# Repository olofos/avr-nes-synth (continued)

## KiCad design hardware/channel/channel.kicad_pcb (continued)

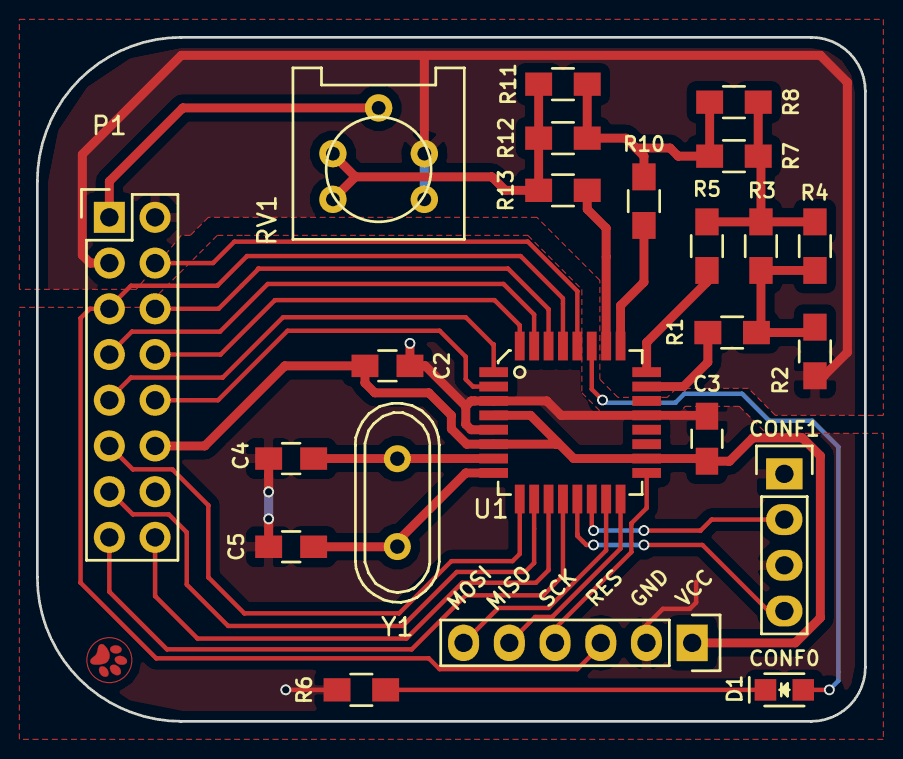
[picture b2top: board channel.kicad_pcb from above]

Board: 2 copper layers, 46.0 x 38.0 mm, 23 parts (0 on the bottom side), 32 nets.

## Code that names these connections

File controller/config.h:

#ifndef CONFIG_H_
#define CONFIG_H_

#include <avr/pgmspace.h>

#include "../common-config.h"

#define MAJOR_VERSION 0
#define MINOR_VERSION 1
#define COPYRIGHT_YEAR "2016-17"
#define AUTHOR "OOS"

#define BAUD 19200UL
#define SCL_CLOCK  100000UL

#define LOG_USE_I2C
#define LOG_USE_SSD1306
#define LOG_USE_BUF


//// Pins /////////////////////////////////////////////////////////////////////

// Bus out

#define PINS_BUS_PORT      PORTD
#define PINS_BUS_PIN       PIND
#define PINS_BUS_DDR       DDRD

#define PIN_BUS0           PORTD0
#define PIN_BUS1           PORTD1
#define PIN_BUS2           PORTD2
#define PIN_BUS3           PORTD3
#define PIN_BUS4           PORTD4
#define PIN_BUS5           PORTD5
#define PIN_BUS6           PORTD6
#define PIN_BUS7           PORTD7

#define PINS_BUS_MASK      (_BV(PIN_BUS0) | _BV(PIN_BUS1) | _BV(PIN_BUS2) | _BV(PIN_BUS3) | _BV(PIN_BUS4) | _BV(PIN_BUS5) | _BV(PIN_BUS6) | _BV(PIN_BUS7))

// Bus clock

#define PIN_DCLK           PORTB0
#define PIN_DCLK_PORT      PORTB
#define PIN_DCLK_PIN       PINB
#define PIN_DCLK_DDR       DDRB

// Frame clock

#define PIN_FCLK           PORTC3
#define PIN_FCLK_PORT      PORTC
#define PIN_FCLK_PIN       PINC
#define PIN_FCLK_DDR       DDRC

// SPI + SD card

#define PIN_SD_CD          PORTB1
#define PIN_SD_CD_PORT     PORTB
#define PIN_SD_CD_PIN      PINB
#define PIN_SD_CD_DDR      DDRB

#define PIN_SD_CS          PORTB2
#define PIN_SD_CS_PORT     PORTB
#define PIN_SD_CS_PIN      PINB
#define PIN_SD_CS_DDR      DDRB

#define PIN_MOSI          PORTB3
#define PIN_MOSI_PORT     PORTB
#define PIN_MOSI_PIN      PINB
#define PIN_MOSI_DDR      DDRB

#define PIN_MISO          PORTB4
#define PIN_MISO_PORT     PORTB
#define PIN_MISO_PIN      PINB
#define PIN_MISO_DDR      DDRB

#define PIN_SCK           PORTB5
#define PIN_SCK_PORT      PORTB
#define PIN_SCK_PIN       PINB
#define PIN_SCK_DDR       DDRB

// I2C

#define PIN_SDA           PORTC4
#define PIN_SDA_PORT      PORTC
#define PIN_SDA_PIN       PINC
#define PIN_SDA_DDR       DDRC

#define PIN_SCL           PORTC5
#define PIN_SCL_PORT      PORTC
#define PIN_SCL_PIN       PINC
#define PIN_SCL_DDR       DDRC

// IO interrupt

#define PIN_IO_INT        PORTC0
#define PIN_IO_INT_PORT   PORTC
#define PIN_IO_INT_PIN    PINC
#define PIN_IO_INT_DDR    DDRC

// LED

#define PIN_LED           PORTC1
#define PIN_LED_PORT      PORTC
#define PIN_LED_PIN       PINC
#define PIN_LED_DDR       DDRC

// Channel reset

#define PIN_CH_RESET      PORTC2
#define PIN_CH_RESET_PORT PORTC
#define PIN_CH_RESET_PIN  PINC
#define PIN_CH_RESET_DDR  DDRC



#endif

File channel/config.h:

#ifndef CONFIG_H_
#define CONFIG_H_

// GPIOR0 bits

#define CONF0_BIT          0
#define CONF1_BIT          1
#define FRAME_FLAG_BIT     2
#define SHIFT_MODE_BIT     7

#ifdef AVR

// Audio out

#define PINS_DAC_PORT      PORTC
#define PINS_DAC_DDR       DDRC

#define PIN_DAC0           PORTC0
#define PIN_DAC1           PORTC1
#define PIN_DAC2           PORTC2
#define PIN_DAC3           PORTC3

#define PINS_DAC_MASK      (_BV(PIN_DAC0) | _BV(PIN_DAC1) | _BV(PIN_DAC2) | _BV(PIN_DAC3))


// Bus in

#define PINS_BUS_PORT      PORTD
#define PINS_BUS_PIN       PIND
#define PINS_BUS_DDR       DDRB

#define PIN_BUS0           PORTD0
#define PIN_BUS1           PORTD1
#define PIN_BUS2           PORTD2
#define PIN_BUS3           PORTD3
#define PIN_BUS4           PORTD4
#define PIN_BUS5           PORTD5
#define PIN_BUS6           PORTD6
#define PIN_BUS7           PORTD7

#define PINS_BUS_MASK      (_BV(PIN_BUS0) | _BV(PIN_BUS1) | _BV(PIN_BUS2) | _BV(PIN_BUS3) | _BV(PIN_BUS4) | _BV(PIN_BUS5) | _BV(PIN_BUS6) | _BV(PIN_BUS7))

// Bus clock

#define PIN_DCLK           PORTB0
#define PIN_DCLK_PORT      PORTB
#define PIN_DCLK_PIN       PINB
#define PIN_DCLK_DDR       DDRB

// Frame clock

#define PIN_FCLK           PORTC5
#define PIN_FCLK_PORT      PORTC
#define PIN_FCLK_PIN       PINC
#define PIN_FCLK_DDR       DDRC

// LED

#define PIN_LED           PORTC4
#define PIN_LED_PORT      PORTC
#define PIN_LED_PIN       PINC
#define PIN_LED_DDR       DDRC

// Config bits

#define PIN_CONF0           PORTB1
#define PIN_CONF0_PORT      PORTB
#define PIN_CONF0_PIN       PINB
#define PIN_CONF0_DDR       DDRB

#define PIN_CONF1           PORTB2
#define PIN_CONF1_PORT      PORTB
#define PIN_CONF1_PIN       PINB
#define PIN_CONF1_DDR       DDRB

#endif
#endif

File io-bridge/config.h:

#ifndef CONFIG_H_
#define CONFIG_H_

#include "../common-config.h"

#define uart_tx_cbuf_LEN 256
#define uart_rx_cbuf_LEN 256

#define BAUD 38400UL

#define LOG_USE_UART

// I2C

#define PIN_SDA           PORTC4
#define PIN_SDA_PORT      PORTC
#define PIN_SDA_PIN       PINC
#define PIN_SDA_DDR       DDRC

#define PIN_SCL           PORTC5
#define PIN_SCL_PORT      PORTC
#define PIN_SCL_PIN       PINC
#define PIN_SCL_DDR       DDRC

// IO interrupt

#define PIN_IO_INT        PORTD2
#define PIN_IO_INT_PORT   PORTD
#define PIN_IO_INT_PIN    PIND
#define PIN_IO_INT_DDR    DDRD

// UART

#define PIN_RX            PORTD0
#define PIN_RX_PORT       PORTD
#define PIN_RX_PIN        PIND
#define PIN_RX_DDR        DDRD

#define PIN_TX            PORTD1
#define PIN_TX_PORT       PORTD
#define PIN_TX_PIN        PIND
#define PIN_TX_DDR        DDRD

// Switches

#define PINS_SW_PORT      PORTB
#define PINS_SW_PIN       PINB
#define PINS_SW_DDR       DDRB

#define PIN_SW1           PORTB0
#define PIN_SW1_PORT      PORTB
#define PIN_SW1_PIN       PINB
#define PIN_SW1_DDR       DDRB

#define PIN_SW2           PORTB1
#define PIN_SW2_PORT      PORTB
#define PIN_SW2_PIN       PINB
#define PIN_SW2_DDR       DDRB

#define PIN_SW3           PORTB6
#define PIN_SW3_PORT      PORTB
#define PIN_SW3_PIN       PINB
#define PIN_SW3_DDR       DDRB

#define PIN_SW4           PORTB7
#define PIN_SW4_PORT      PORTB
#define PIN_SW4_PIN       PINB
#define PIN_SW4_DDR       DDRB

#define PINS_SW_MASK      (_BV(PIN_SW1) | _BV(PIN_SW2) | _BV(PIN_SW3) | _BV(PIN_SW4))


// LED:s

#define PINS_LED_PORT      PORTC
#define PINS_LED_PIN       PINC
#define PINS_LED_DDR       DDRC

#define PIN_LED1           PORTC0
#define PIN_LED1_PORT      PORTC
#define PIN_LED1_PIN       PINC
#define PIN_LED1_DDR       DDRC

#define PIN_LED2           PORTC1
#define PIN_LED2_PORT      PORTC
#define PIN_LED2_PIN       PINC
#define PIN_LED2_DDR       DDRC

#define PIN_LED3           PORTC2
#define PIN_LED3_PORT      PORTC
#define PIN_LED3_PIN       PINC
#define PIN_LED3_DDR       DDRC

#define PIN_LED4           PORTC3
#define PIN_LED4_PORT      PORTC
#define PIN_LED4_PIN       PINC
#define PIN_LED4_DDR       DDRC

#define PINS_LED_MASK      (_BV(PIN_LED1) | _BV(PIN_LED2) | _BV(PIN_LED3) | _BV(PIN_LED4))

#endif

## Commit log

2016-11-20 * Refactored lib/fat32.c * Added a cluster cache
2016-11-20 * Added .gitignore
2016-11-20 * Fixed an off-by-one error in cluster cache affecting files consising of a single cluster
2016-11-20 * Removed some debug output
2016-11-21 * Refactored SSD1306 code
2016-11-21 * Added log_nl
2016-11-21 * Added more text functions
2016-11-21 * Added basic menu system * General cleanup
2016-11-23 * Added a menu system * Added an 8 Hz system timer * Refactoring
2017-06-12 various small changes
2017-06-13 Rewrite main interrupt in assembler
2017-06-15 A bit of refactoring
2017-06-15 Fixed a few bugs
2017-06-15 Build common functions to a library
2017-06-30 Fixed a glitch in the output of the pulse and noise channels
    When the volume was changed while the channel was outputting a high,
    the wrong volume was ouput until the next time the output went low.
    Previously the volume was simply ORed into the output register, but
    now the register is first cleared.
2017-07-07 * Add support for sweep on pulse channels
2017-07-07 * Update period of triangle channel when lower byte is changed This fixes a sound issue in Mega Man II
2017-07-07 * Add ssd1306_puts_P to print string from flash * Fixed a bug in ssd1306_text_putc A missing cast prevented characters larger than 127 to print correctly
2017-07-07 * Added an about screen
2017-07-08 Slight cleanup of fat32.c
2017-07-08 * Refactor menu code
2017-07-08 * Add fuse data to makefile
2017-07-08 *Added version and copyright information
2017-07-08 * Added support for menu data in EEPROM and flash
2017-07-08 * Add delays to silence channels when starting up and after finishing playing a song
2017-07-08 * Changed about screen layou
2017-07-08 * Added menus to play songs from playlist, and to add and remove tracks from the list * Change main menu to store data in flash
2017-07-08 * Add *.a to .gitignore * A bit more verbose avrdude output
2017-07-11 * Added loggnig to circular buffer and a menu item to show the log
2017-07-11 * Fixed missing 0 at end of filename * Added some extra comments
2017-07-11 * Don't hardcode line width in the menu code * Got the previous position when the current position has disappeared
2017-07-11 * Unused functions and variables should only produce an error
2017-07-15 * Added schematics and PCB layouts (Rev A)
2017-07-15 * Fix file permissions
2017-07-15 * Added a block diagram
2017-07-15 * Updated .gitignore
2017-07-16 * Clean up log.h
2017-07-16 * Corrected the duty cycle setting when mode=11
2017-07-17 * Started writing a README file
2017-07-17 * A bit more writing in the README
2017-07-17 * More about the pulse channels
2017-07-17 * More text in the README file
2017-07-17 * Added programs and scripts to create binary data files from NSF files
    The new NSF player is based on Game_Music_Emu 0.5.2 by Shay Green
2017-07-17 * Updated README to mention the newly added scripts
2017-07-17 * Fix link error in README
2017-07-18 * Added bin_play prgram to play back binary files
2017-07-18 * Added a class to load and save song files in ascii and binary
2017-07-18 * Use new dat_file class in nsf_play and bin_play
2017-07-18 * Maintain a fixed frame rate to allow for silent frames
2017-07-18 * Update .gitignore
2017-07-19 * Fix detection of empty frames in nsf_play
2017-07-19 * Add LOOP_FRAME and LOOP_BYTE
2017-07-19 * Use dat_file class in dat_to_bin
2017-07-19 * Use dat_file in detect_loops
2017-07-19 * Take output file as a parameter in bin_play
2017-07-20 * Add basic ALSA support to bin_play
2017-07-20 * Let bin_play loop the track
2017-07-20 * Timeout in bin_play
2017-07-20 * Find loop before playing and allow timeout in middle of track
2017-07-28 * Corrected config table in README
2017-07-28 * Got rid of some code repetition
2017-07-28 * Use a wave table for the triangle channel
2017-07-28 * Factored out some functions to handle frame updates
2017-07-28 * Whitespace cleanup
2017-10-04 * Save some cycles in the interrupt by using r6 as a fixed temporary register * Fixed a typo in main.c
2018-08-24 Script to analyse bank switching
2018-08-25 Refactored channel code
    - Introduced a union containing the lower and higher byte of the channel period
    - Improved assembly interrupt code
2018-08-25 Started adding a function for scrolling text
2018-08-25 Added 48x48 pixel logo
2018-08-25 Refactored menu code
2018-08-25 Started writing a design document about implementing a boot loader for the channels.
2018-08-25 Started writing bootloader
2018-08-25 More thoughts about UART IO-bridge
2018-08-25 Update I2C slave code
2018-08-25 Missing config update
2018-08-25 Added better support form UART bridge
2018-08-25 Refactor and update I2C master code
2018-08-25 Added CONF_MASK and PINS_DAC_PIN
2018-08-25 Added missing header file
2018-08-25 Added missing void. Whitespace cleanup
2018-08-25 Factored out common function in log_i2c_*
2018-08-25 Fixed bug in i2c-master.c
2018-08-25 Remove -Werror during development
2018-08-25 Remove unnecessary delays
2018-08-25 Added a parameter to error_led_loop to signal different errors
2018-08-25 Don't read the port in set_outputs, set_inputs, enable_pullups, disable_pullups if writing to the whole port
2018-08-25 Protect macros with do { ... } while(0)
2018-08-25 Added function cbuf_peek
2018-08-25 Started added support for programming the channels
2018-08-25 Added are_high and are_low
2018-08-25 Fixed a typo in channel/config.h: the bus should use DDRD
2018-08-25 Added missing void in prototypes
2018-08-25 Added basic handshake and enumeration of channels
2018-08-25 Remove unused code
2018-08-25 Add support for reading flash
2018-08-25 Only start bootloader if we see BOOTLOADER_FLAG and start app if we see 0x00. Otherwise blink led to report error.
2018-08-25 Actually add BOOTLOADER_FLAG
2018-08-25 The minimum bit rate is 1
2018-08-25 Make sure to release the bus before reading command
2018-08-25 Abstract out channel timer settings
2018-08-25 Add symbolic names for GPIO0
2018-08-25 Factor out APU code to its own file and make it compile on non-AVR
2018-08-25 Move declarations to header
2018-08-26 Add missing member variable
2018-08-26 Renamed nes_apu.[ch] to nes_apu_channel.[ch]
2018-08-27 Added extra fields for playing on non-AVR hardware
2018-08-27 Write to 4015 should set length counter to zero
2018-08-29 Better code for muting channels
2018-08-31 Reworked sweep unit
2018-10-25 Added Makefile for bootloader
2018-10-25 Added verbose flag to Makefile
2018-10-25 Correct typo copied form datasheet. Reuse zero register
2018-10-25 Update delays in channel updater
2018-10-25 Check correct register in bootloader
2018-10-25 Implement page write
2018-10-26 Config pins are not used in bootloader
2018-10-27 Don't erase flash when burning bootloader
2018-10-27 Reorder sections so that we can use rjmp
2018-10-27 out needs a register!
2018-10-27 Assume pagesize is smaller than 256
2018-10-27 Use a buffer in ram
2018-10-29 Save some byte by inlining error loop
2018-10-29 Move waiting for clock and SPM to sibroutines
